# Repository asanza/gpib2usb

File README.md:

# GPIB (IEEE-488) to usb adapter

We live in wonderful times... Now is possible for us to get pretty good but old and used measurement equipment on e-bay, just for a few bucks. Equipment that otherwise would be out of  the hobbist leage, like 6.5 digit multimeters, oscilloscopes, signal generators... just to name a few.

These old equipment often come with a GPIB interface, which allows to control them from a computer with the corresponding GPIB connection. Regretably, computers do not come with GPIB interfaces, and the adapters available are not cheap.

Here comes this little device to rescue. It is a gpib-to-usb adapter which after connected to the computer via the almighty usb port, it presents itself as a serial port and allows to send GPIB commands to connected GPIB devices.

For now is yet a work in progress.

# Getting Started

The device presents itself as a serial port. The commands are the same as the similar device sold by [Prologix LLC](http://prologix.biz/gpib-usb-controller.html), but compatibility is not guaranteed.

| Command	 | Description |
|----------|-------------|
|++addr 0-31|	Tell controller which device to address|
|++addr	| Query currently configured device address
|++clr	| This command sends the Selected Device Clear (SDC) message to the currently specified GPIB address. Please consult the programming manual for details on how a particular instrument responds to this message.
|++eoi 0/1|	Enable (1) or disable (0) EOI with last byte. Default is 0. This command enables or disables the assertion of the EOI signal with the last character of any command sent over GPIB port. Some instruments require EOI signal to be asserted in order to properly detect the end of a command.
|++eoi	|Query current EOI setting
|++eos 0/1/2/3	|EOS terminator — 0:CR+LF, 1:CR, 2:LF, 3:None. Default is 0. This command specifies GPIB termination characters. When data from host is received over USB, all non-escaped LF, CR and ESC characters are removed and GPIB terminators, as specified by this command, are appended before sending the data to instruments. This command does not affect data from instruments received over GPIB port.|
|++eos	|Query current EOS setting
|++ifc	|Issue interface clear. This command asserts GPIB IFC signal for 150 microseconds making the gpib2usb controller the Controller-In-Charge on the GPIB bus.
|++loc	|Return device to local mode
|++read  [eoi/char]| This command can be used to read data from an instrument until: EOI is detected or timeout expires, or A specified character is read or timeout expires, or Timeout expires. Timeout is set using the read_tmo_ms command and applies to inter-character delay, i.e., the delay since the last character was read. Timeout is not be confused with the total time for which data is read. |
|++read_tmo_ms [1-3000]| This command specifies the timeout value, in milliseconds, to be used in the read command and spoll command. Timeout may be set to any value between 1 and 3000 milliseconds.|
|++spoll	|Read status byte by serial polling the device
|++srq	|Query status of SRQ line. 0: Not asserted, 1:Asserted
|++trg	|Issue device trigger
|++ver	|Query GPIB-USB controller version
|++help	|Print help about commands

To send binary data to instruments following characters must be escaped by preceding them with an ESC character:
CR (ASCII 13), LF (ASCII 10), ESC (ASCII 27), ‘+’ (ASCII 43)

# Contributing

# Know issues

## Disable modem manager in linux.

In order to detect new devices, modem manager issues two AT commands to each new ACM device detected. This blocks the serial port and causes it to be unavailable the first seconds. This is somewhat annoying. Fortunately it is possible to disable this behaviour. You need to create a new file:

```
/etc/udev/rules.d/77-mm-usb-device-blacklist.rules
```
and put following content in it:

```
with content:
# gpib2usb converter
ATTRS{idVendor}=="1209", ATTRS{idProduct}=="0001", ENV{ID_MM_DEVICE_IGNORE}="1"
```

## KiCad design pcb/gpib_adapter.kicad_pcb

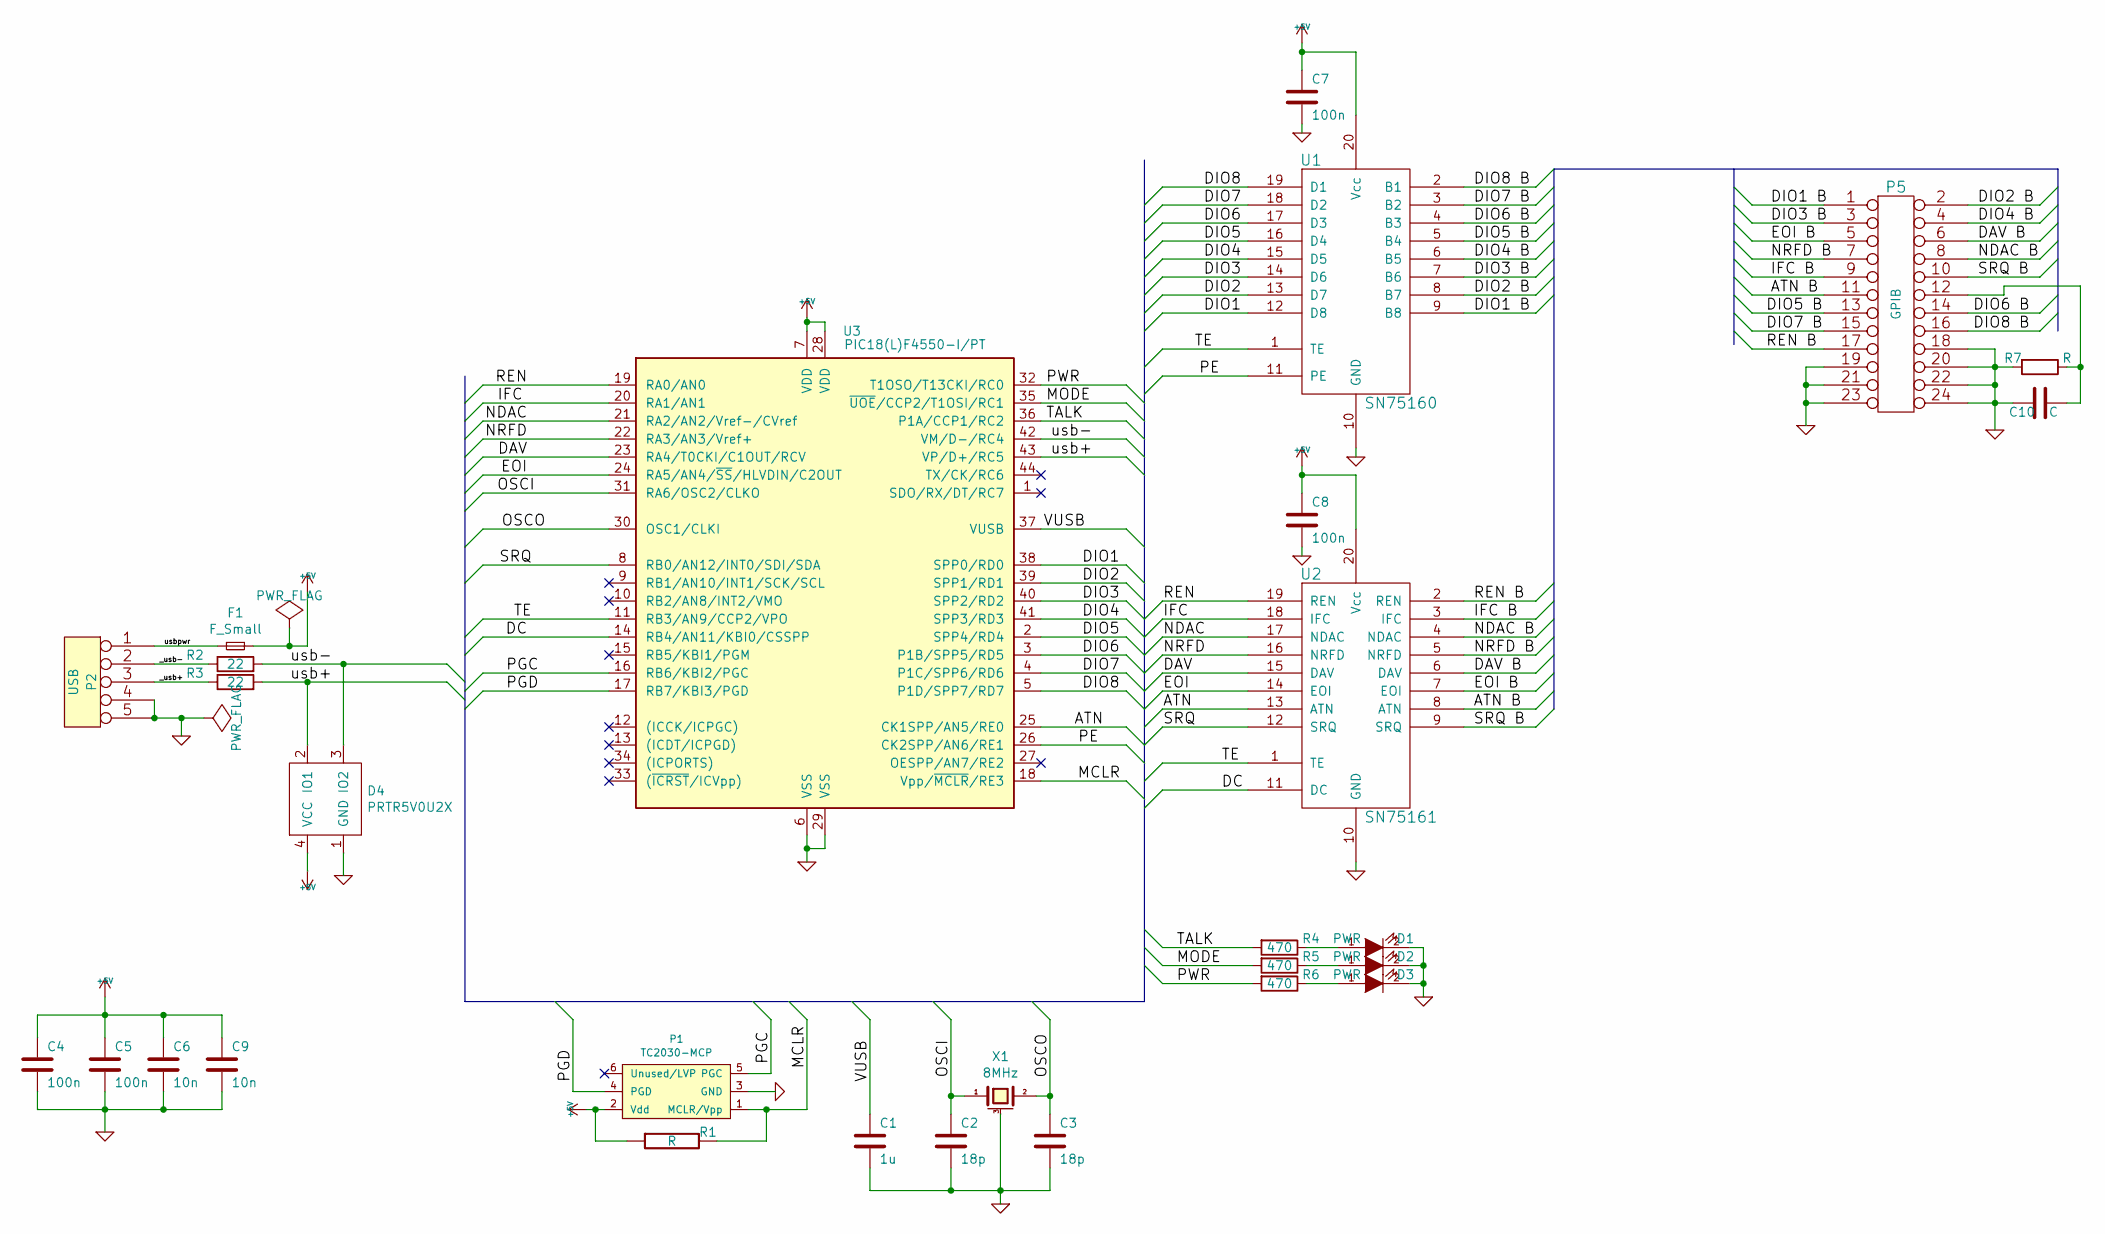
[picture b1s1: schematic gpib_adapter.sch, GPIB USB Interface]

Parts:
C1: 1u; C_0805
C2, C3: 18p; C_0805
C4, C5, C7, C8: 100n; C_0805
C6, C9: 10n; C_0805
C10: C; C_1206
D1, D2, D3: PWR; LED-5MM
D4: PRTR5V0U2X
F1: F_Small; R_1210
P1: TC2030-MCP; TC2030-NL_SMALL
P2: USB; USB_B
P5: GPIB; gpib_conn_male; Digikey 1024RFA-ND
R1: R; R_0805
R2, R3: 22; R_0805
R4, R5, R6: 470; R_0805
R7: R; R_1206
U1: SN75160; SOIC-20_7.5x12.8mm_Pitch1.27mm
U2: SN75161; SOIC-20_7.5x12.8mm_Pitch1.27mm
U3: PIC18(L)F4550-I/PT; TQFP-44_10x10mm_Pitch0.8mm
X1: 8MHz; Crystal_SMD_5032_4Pads

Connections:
+5V: C4.1, C5.1, C6.1, C7.1, C8.1, C9.1, D4.4 (VCC), F1.2, P1.2 (Vdd), R1.1, U1.20 (Vcc), U2.20 (Vcc), U3.7 (VDD), U3.28 (VDD)
/ATN: U2.13 (ATN), U3.25 (CK1SPP/AN5/RE0)
/ATN B: P5.11, U2.8 (ATN)
/DAV: U2.15 (DAV), U3.23 (RA4/T0CKI/C1OUT/RCV)
/DAV B: P5.6, U2.6 (DAV)
/DC: U2.11 (DC), U3.14 (RB4/AN11/KBI0/CSSPP)
/DIO1: U1.12 (D8), U3.38 (SPP0/RD0)
/DIO1 B: P5.1, U1.9 (B8)
/DIO2: U1.13 (D7), U3.39 (SPP1/RD1)
/DIO2 B: P5.2, U1.8 (B7)
/DIO3: U1.14 (D6), U3.40 (SPP2/RD2)
/DIO3 B: P5.3, U1.7 (B6)
/DIO4: U1.15 (D5), U3.41 (SPP3/RD3)
/DIO4 B: P5.4, U1.6 (B5)
/DIO5: U1.16 (D4), U3.2 (SPP4/RD4)
/DIO5 B: P5.13, U1.5 (B4)
/DIO6: U1.17 (D3), U3.3 (P1B/SPP5/RD5)
/DIO6 B: P5.14, U1.4 (B3)
/DIO7: U1.18 (D2), U3.4 (P1C/SPP6/RD6)
/DIO7 B: P5.15, U1.3 (B2)
/DIO8: U1.19 (D1), U3.5 (P1D/SPP7/RD7)
/DIO8 B: P5.16, U1.2 (B1)
/EOI: U2.14 (EOI), U3.24 (RA5/AN4/~SS~/HLVDIN/C2OUT)
/EOI B: P5.5, U2.7 (EOI)
/IFC: U2.18 (IFC), U3.20 (RA1/AN1)
/IFC B: P5.9, U2.3 (IFC)
/MCLR: P1.1 (MCLR/Vpp), R1.2, U3.18 (Vpp/~MCLR~/RE3)
/MODE: R5.2, U3.35 (~UOE~/CCP2/T1OSI/RC1)
/NDAC: U2.17 (NDAC), U3.21 (RA2/AN2/Vref-/CVref)
/NDAC B: P5.8, U2.4 (NDAC)
/NRFD: U2.16 (NRFD), U3.22 (RA3/AN3/Vref+)
/NRFD B: P5.7, U2.5 (NRFD)
/OSCI: C2.1, U3.31 (RA6/OSC2/CLKO), X1.1
/OSCO: C3.1, U3.30 (OSC1/CLKI), X1.2
/PE: U1.11 (PE), U3.26 (CK2SPP/AN6/RE1)
/PGC: P1.5 (PGC), U3.16 (RB6/KBI2/PGC)
/PGD: P1.4 (PGD), U3.17 (RB7/KBI3/PGD)
/PWR: R6.2, U3.32 (T1OSO/T13CKI/RC0)
/REN: U2.19 (REN), U3.19 (RA0/AN0)
/REN B: P5.17, U2.2 (REN)
/SRQ: U2.12 (SRQ), U3.8 (RB0/AN12/INT0/SDI/SDA)
/SRQ B: P5.10, U2.9 (SRQ)
/TALK: R4.2, U3.36 (P1A/CCP1/RC2)
/TE: U1.1 (TE), U2.1 (TE), U3.11 (RB3/AN9/CCP2/VPO)
/VUSB: C1.1, U3.37 (VUSB)
/_usb+: P2.3, R3.1
/_usb-: P2.2, R2.1
/usb+: D4.2 (IO1), R3.2, U3.43 (VP/D+/RC5)
/usb-: D4.3 (IO2), R2.2, U3.42 (VM/D-/RC4)
/usbpwr: F1.1, P2.1
GND: C1.2, C2.2, C3.2, C4.2, C5.2, C6.2, C7.2, C8.2, C9.2, C10.2, D1.2 (K), D2.2 (K), D3.2 (K), D4.1 (GND), P1.3 (GND), P2.4, P2.5, P5.18, P5.19, P5.20, P5.21, P5.22, P5.23, P5.24, R7.2, U1.10 (GND), U2.10 (GND), U3.6 (VSS), U3.29 (VSS), X1.3 (case)
unnamed: C10.1, P5.12, R7.1
unnamed: D1.1 (A), R4.1
unnamed: D2.1 (A), R5.1
unnamed: D3.1 (A), R6.1

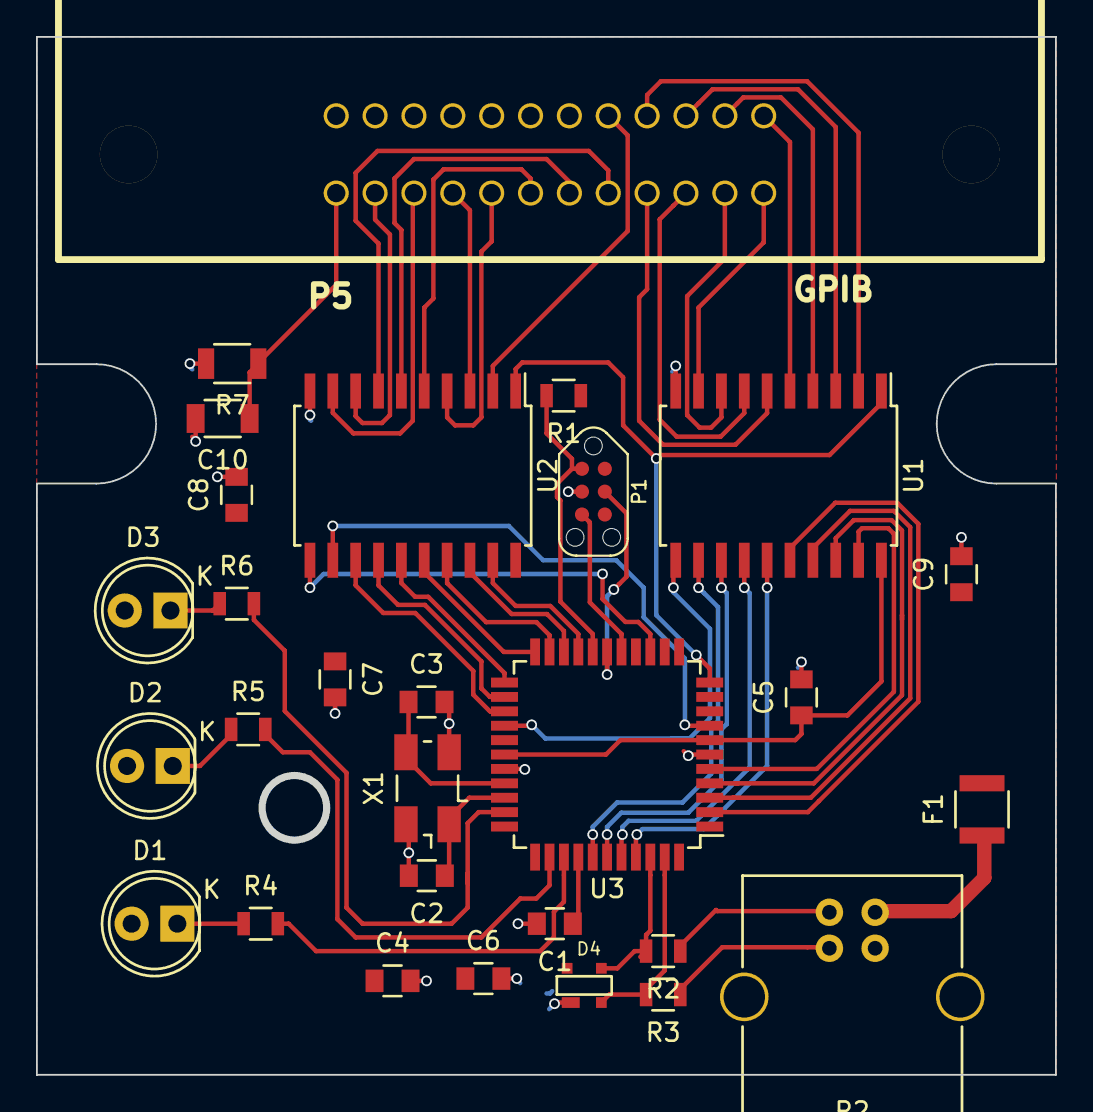
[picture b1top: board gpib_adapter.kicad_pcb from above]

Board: 2 copper layers, 56.3 x 57.4 mm, 29 parts (0 on the bottom side), 55 nets.

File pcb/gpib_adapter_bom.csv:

"Id";"Designator";"Package";"Quantity";"Designation";"Supplier and ref";
1;"P5";"gpib_conn_male";1;"GPIB";;;
2;"C2,C3";"C_0805";2;"18p";;;
3;"C7,C8,C4,C5";"C_0805";4;"100n";;;
4;"R1";"R_0805";1;"R";;;
5;"R2,R3";"R_0805";2;"22";;;
6;"R4,R5,R6";"R_0805";3;"470";;;
7;"U1";"SOIC-20_7.5x12.8mm_Pitch1.27mm";1;"SN75160";;;
8;"U2";"SOIC-20_7.5x12.8mm_Pitch1.27mm";1;"SN75161";;;
9;"P1";"TC2030-NL_SMALL";1;"TC2030-MCP";;;
10;"D4";"PRTR5V0U2X";1;"PRTR5V0U2X";;;
11;"F1";"R_1210";1;"F_Small";;;
12;"D3,D1,D2";"LED-5MM";3;"PWR";;;
13;"U3";"TQFP-44_10x10mm_Pitch0.8mm";1;"PIC18(L)F4550-I/PT";;;
14;"X1";"Crystal_SMD_5032_4Pads";1;"8MHz";;;
15;"C1";"C_0805";1;"1u";;;
16;"C6,C9";"C_0805";2;"10n";;;
17;"C10";"C_1206";1;"C";;;
18;"R7";"R_1206";1;"R";;;
19;"P2";"USB_B";1;"USB";;;

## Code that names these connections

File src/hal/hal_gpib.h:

/*
 * hal_gpib.h
 *
 * Copyright (c) 2016, Diego F. Asanza. All rights reserved.
 *
 * This program is free software; you can redistribute it and/or
 * modify it under the terms of the GNU Lesser General Public
 * License as published by the Free Software Foundation; either
 * version 2.1 of the License, or (at your option) any later version.
 *
 * This library is distributed in the hope that it will be useful,
 * but WITHOUT ANY WARRANTY; without even the implied warranty of
 * MERCHANTABILITY or FITNESS FOR A PARTICULAR PURPOSE.  See the GNU
 * Lesser General Public License for more details.
 *
 * You should have received a copy of the GNU Lesser General Public
 * License along with this library; if not, write to the Free Software
 * Foundation, Inc., 51 Franklin Street, Fifth Floor, Boston,
 * MA 02110-1301  USA
 *
 * Created on June 29, 2016, 9:28 PM
 */


#ifndef hal_gpib_H
#define hal_gpib_H

/* exported pin interface */
#define ATN_PIN     0x01
#define REN_PIN     0x02
#define IFC_PIN     0x04
#define SRQ_PIN     0x08

#define DAV_PIN     0x10
#define NDAC_PIN    0x20
#define NRFD_PIN    0x40

#define EOI_PIN     0x80


#define GPIO1   11
#define GPIO2   12
#define GPIO3   13
#define GPIO4   14
#define GPIO5   15
#define TXD     16
#define RXD     17

typedef enum {
	CONTROLLER = 0x01,
	DEVICE = 0x02,
}hal_gpib_driver_mode;

typedef enum {
	TALKER = 0x04,
	LISTENER = 0x08
}hal_gpib_data_direction;

void hal_gpib_set_driver_direction(hal_gpib_data_direction direction);
void hal_gpib_init(void);
int hal_gpib_is_signal_true(int pin);
void hal_gpib_set_signal_false(int pin);
void hal_gpib_set_signal_true(int pin);
void hal_gpib_put_data(char c);
char hal_gpib_read_data(void);
void hal_gpib_set_driver_mode(hal_gpib_driver_mode mode);



#endif // hal_gpib_H

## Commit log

2015-09-12 change processor
2015-09-14 adding some code
2015-09-14 new message
2015-09-17 update gpib interface
2015-09-23 added unit test framework
2015-10-04 - implementing hal interface
2015-10-10 changing project structure
2015-10-10 - change api for input functions. fix broken tests
2015-10-10 - formatting code
2015-10-10 fix hardware issues
2015-10-10 fix: fix gpib adapter connections
2015-10-11 - fix: AVR should write to PORT registers and read from PIN registers.
2015-10-11 - new interface and gpib implementation. try 2.
2015-10-11 - prototyping interface changes
2015-12-01 updating hardware
2015-12-04 do some refactoring
2015-12-04 refactor driver mode function
2015-12-04 fix pin definitions
2015-12-04 invert data lines. All gpib works with inverted logic
2015-12-04 remove diagnostic breakpoint
2015-12-04 fix address
2015-12-05 add timer files
2015-12-05 working read
2016-06-22 change microcontroller to pic18F to save costs
2016-06-22 add enclosure drawing
2016-06-24 Update pcb files. New version based on pic 18f4550.
2016-06-24 change srq to pin rb0 to make it use the external interrupt 0
2016-06-25 update cad files
2016-06-25 updated cad files
2016-06-27 update documentation
2016-06-27 Update readme file.
2016-06-29 importing pic18f4550 software
2016-06-29 create hal
2016-06-30 fix test fixture
2016-07-01 input parser
2016-07-02 remove automatic generated files from git
2016-07-05 Add string to u
2016-07-05 add string to integer function.
2016-07-09 feat: address command working
2016-07-09 add uart for debugging
2016-07-10 new gpib subsystem structure.
2016-07-10 first try to gpib communication.
2016-07-31 Refactoring code for use in a no multithreading system.
    The gpib library code was copied of a previous implementation based on FreeRTOS. As this implementation does not use a scheduler, all functions are not blocking in nature.
2016-09-08 add hardware profile file
2016-09-08 Change processor to PIC18F4550
2016-09-08 fix led color issues
2016-09-09 implement ++addr command
2016-09-10 fix unit test
2016-09-10 Add atom configuration files
2016-09-10 working on gpib tasks
2016-09-10 add transmission code
2016-09-11 add tx and rx error return codes
2016-09-11 beautify code
2016-09-11 refactor gpib interface
2016-09-11 fix input buffer
2016-09-11 add test
2016-09-11 fix misspelling
2016-09-17 add unit tests
2016-09-17 refactor gpib code. Separate into talk and send state machines.
2016-09-18 add some unit tests for gpib talk function
2016-09-18 add unit tests for gpib talk task.
2016-09-18 add gpib listen code.
2016-09-18 add set mode controller/listener function
2016-09-18 fix whitespaces.
2016-09-18 add copyright notices.
2016-10-05 implement gpib module
2016-10-05 system.c state machine
2016-10-05 move some functionality from the interface to the pc
2016-10-06 reimplement parser
2016-10-06 fixed version, new api
2016-10-06 fix release compilation
2016-10-06 remove unused files
2016-10-08 refactor input module
2016-10-09 add defines for automatically determine repo version and branch.
2016-10-09 refactor sys interface
2016-10-09 add command line programming task
2016-10-09 implemented eoi and eos commands
2016-10-09 move usb task to timer interrupt in order to move gpib functions to blocking api
2016-10-09 testing different ipc
2016-10-10 move input to sysio
2016-10-10 working usb timers
2016-10-10 rebasing changes on blocking main branch
2016-10-10 fix sisio interface
2016-10-10 add critical sections
2016-10-11 read data from gpib back to usb
2016-10-11 read data back from gpib to usb
2016-10-11 implementing get data back from gpib to application
2016-10-11 simplify gpib interface
2016-10-11 revert back to blocking gpib functions
2016-10-11 add documentation
2016-10-17 use app_out_transaction callback to advance state machine.
2016-10-17 connect main with process command module
2016-10-18 add build directory
2016-10-20 add ci integration script
2016-10-20 add build badge status
2016-10-20 fix space
2016-10-20 fix status badge
2016-10-20 fix badge
2016-10-20 fix build script
2016-10-20 fix broken tests
2016-10-20 update ci script
2016-10-20 fix broken test
